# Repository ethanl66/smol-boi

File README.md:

# Smol boi

Custom 40% Keyboard PCB design files designed with KiCad 5.1.4. 

## Description

Smol Boi is a custom personal 40% keyboard PCB designed to provide a compact and efficient layout. This repository contains the KiCad design files including schematic and layout.
Firmware can be found at https://github.com/ethanl66/smolboi-firmware-v1.0

## Features

- 40% layout
- Custom layout with 46 keys
- USB-C connnectivity
- Flashable with DFU mode using USB-C
- Planned features for V2.0: LED indicators, hot-swap sockets, Bluetooth/2.4 GHz dongle, daughterboard, knob

## Contents

- `smolboi-pcb.sch`: Contains the PCB schematic
- `smolboi-pcb.kicad_pcb`: Contains the routing layout

## Acknowledgments

- Inspired by the community of keyboard enthusiasts
- Would not have been possible without r/MechanicalKeyboards

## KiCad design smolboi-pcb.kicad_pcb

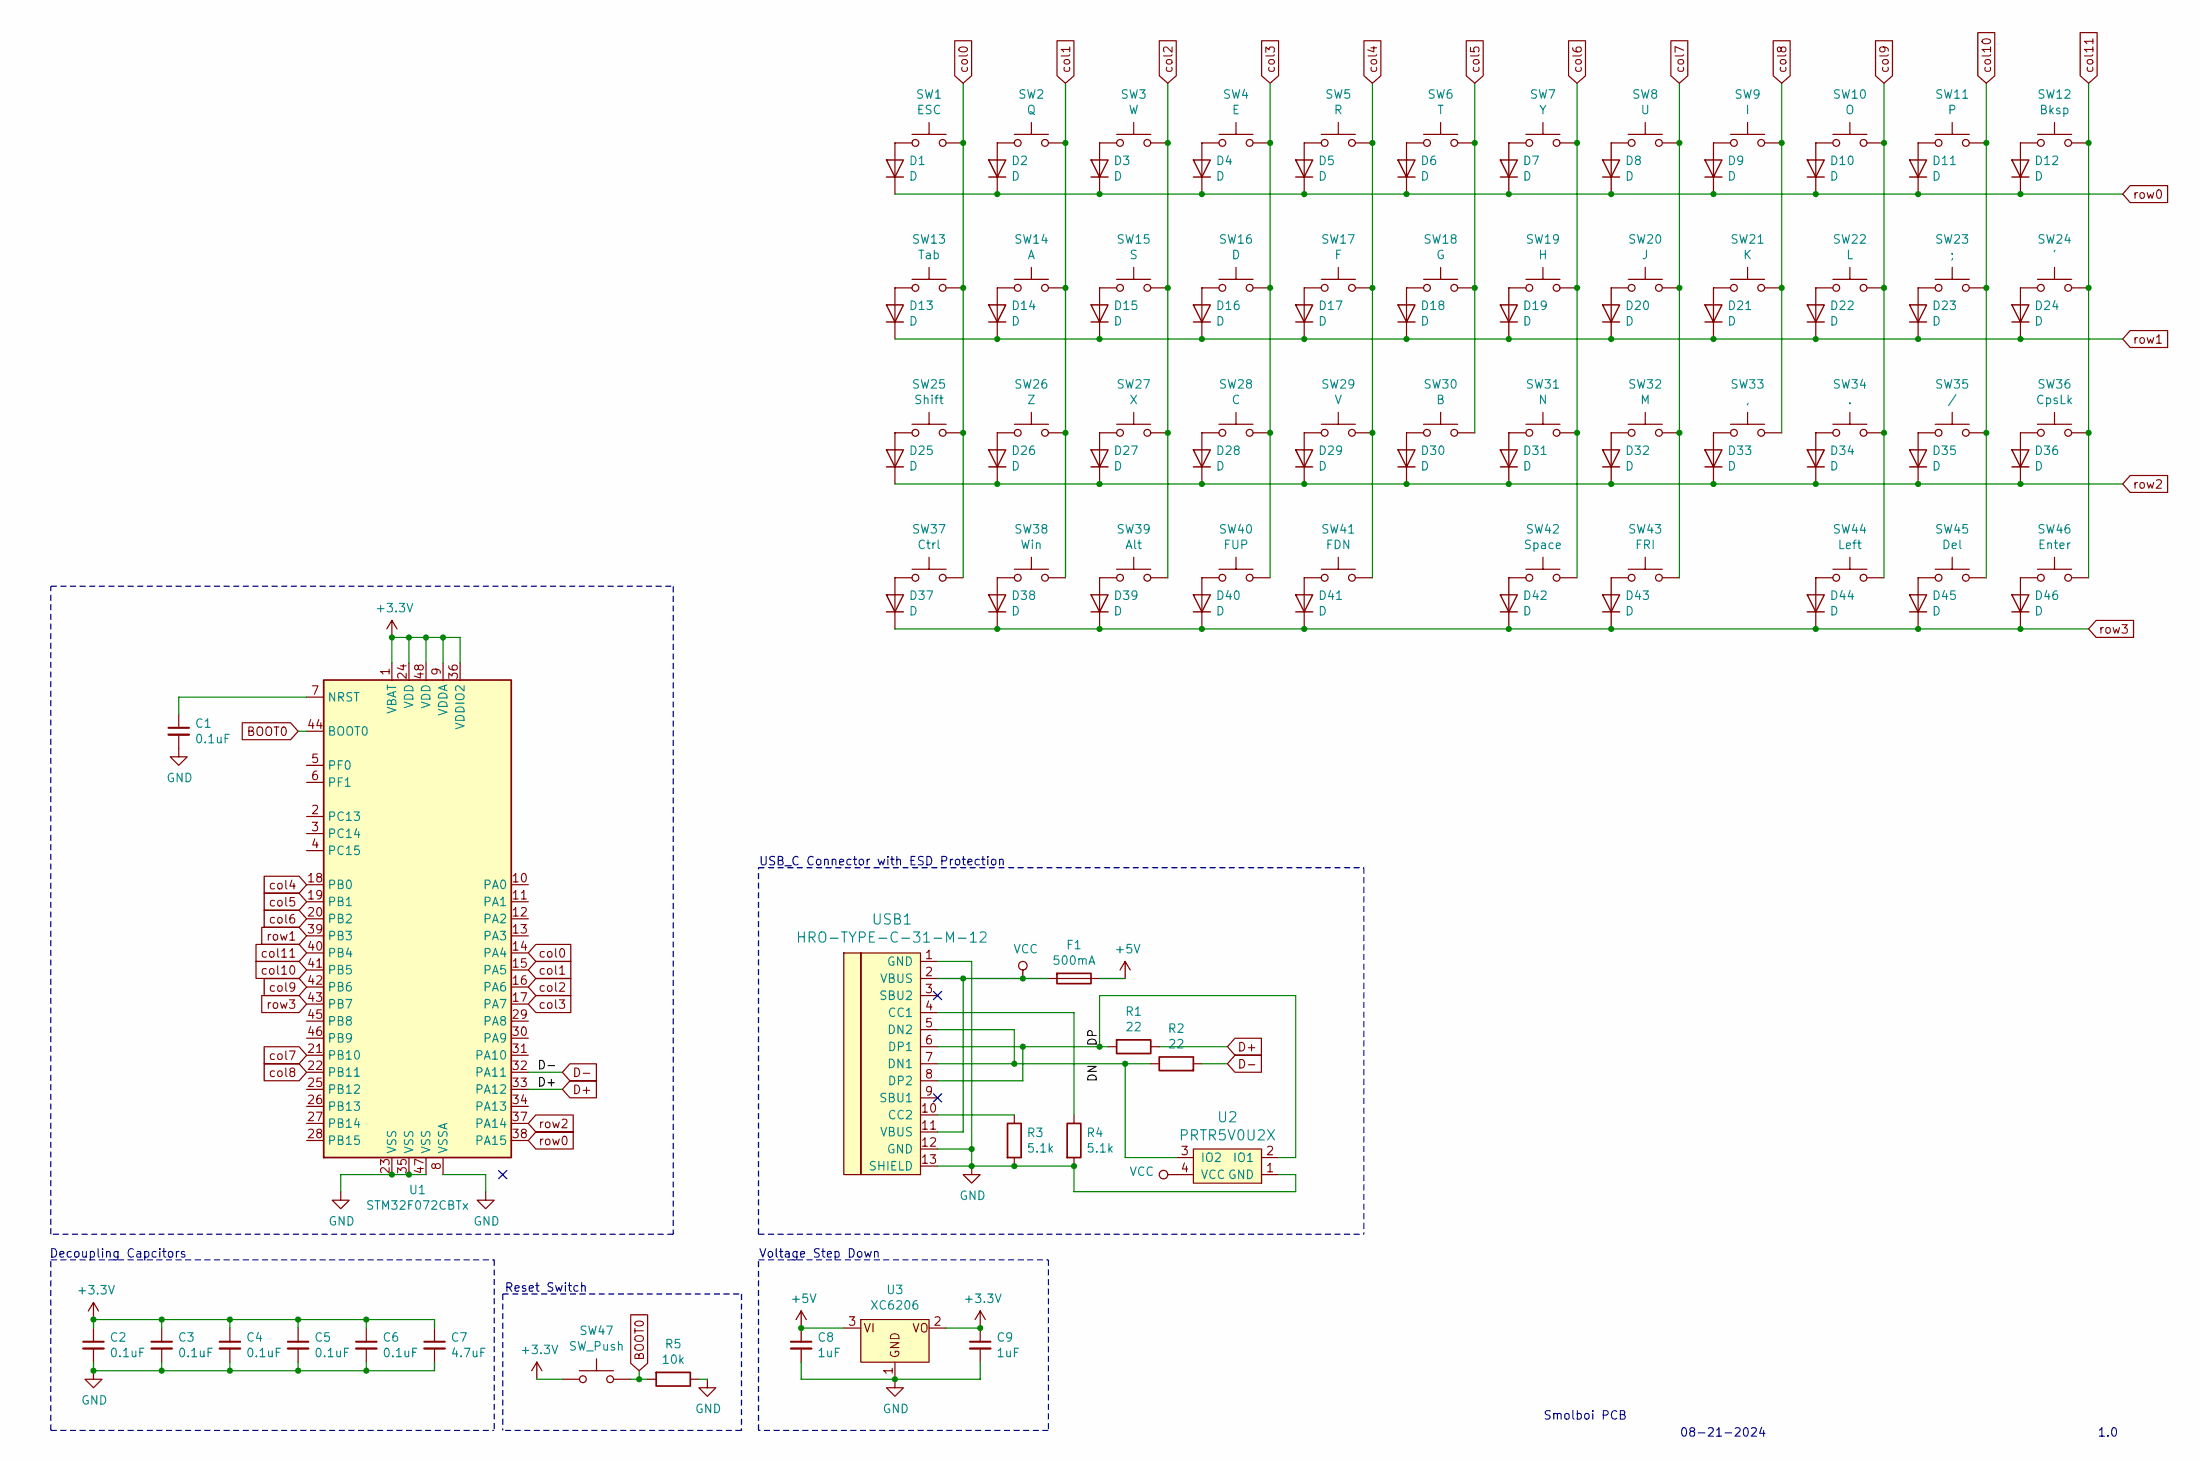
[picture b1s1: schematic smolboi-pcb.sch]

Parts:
C1, C2, C3, C4, C5, C6: 0.1uF; C_0402_1005Metric; LCSC C307331
C7: 4.7uF; C_0402_1005Metric; LCSC C23733
C8, C9: 1uF; C_0402_1005Metric; LCSC C52923
D1, D2, D3, D4, D5, D6, D7, D8, D9, D10, D11, D12, D13, D14, D15, D16, D17, D18, D19, D20, D21, D22, D23, D24, D25, D26, D27, D28, D29, D30, D31, D32, D33, D34, D35, D36, D37, D38, D39, D40, D41, D42, D43, D44, D45, D46: D; D_SOD-123; LCSC C77978
F1: 500mA; Fuse_1206_3216Metric; LCSC C70069
R1, R2: 22; R_0402_1005Metric; LCSC C6117666
R3, R4: 5.1k; R_0402_1005Metric; LCSC C400635
R5: 10k; R_0402_1005Metric; LCSC C850723
SW1: ESC; MXOnly-1U-NoLED
SW2: Q; MXOnly-1U-NoLED
SW3: W; MXOnly-1U-NoLED
SW4: E; MXOnly-1U-NoLED
SW5: R; MXOnly-1U-NoLED
SW6: T; MXOnly-1U-NoLED
SW7: Y; MXOnly-1U-NoLED
SW8: U; MXOnly-1U-NoLED
SW9: I; MXOnly-1U-NoLED
SW10: O; MXOnly-1U-NoLED
SW11: P; MXOnly-1U-NoLED
SW12: Bksp; MXOnly-1.75U-NoLED
SW13: Tab; MXOnly-1.25U-NoLED
SW14: A; MXOnly-1U-NoLED
SW15: S; MXOnly-1U-NoLED
SW16: D; MXOnly-1U-NoLED
SW17: F; MXOnly-1U-NoLED
SW18: G; MXOnly-1U-NoLED
SW19: H; MXOnly-1U-NoLED
SW20: J; MXOnly-1U-NoLED
SW21: K; MXOnly-1U-NoLED
SW22: L; MXOnly-1U-NoLED
SW23: ;; MXOnly-1U-NoLED
SW24: '; MXOnly-1.5U-NoLED
SW25: Shift; MXOnly-1.75U-NoLED
SW26: Z; MXOnly-1U-NoLED
SW27: X; MXOnly-1U-NoLED
SW28: C; MXOnly-1U-NoLED
SW29: V; MXOnly-1U-NoLED
SW30: B; MXOnly-1U-NoLED
SW31: N; MXOnly-1U-NoLED
SW32: M; MXOnly-1U-NoLED
SW33: ,; MXOnly-1U-NoLED
SW34: .; MXOnly-1U-NoLED
SW35: /; MXOnly-1U-NoLED
SW36: CpsLk; MXOnly-1U-NoLED
SW37: Ctrl; MXOnly-1.25U-NoLED
SW38: Win; MXOnly-1.25U-NoLED
SW39: Alt; MXOnly-1.25U-NoLED
SW40: FUP; MXOnly-1U-NoLED
SW41: FDN; MXOnly-1U-NoLED
SW42: Space; MXOnly-2U-NoLED
SW43: FRI; MXOnly-1U-NoLED
SW44: Left; MXOnly-1U-NoLED
SW45: Del; MXOnly-1U-NoLED
SW46: Enter; MXOnly-1U-NoLED
SW47: SW_Push; SW_SPST_SKQG_WithStem; LCSC C115351
U1: STM32F072CBTx; LQFP-48_7x7mm_P0.5mm; LCSC C81720
U2: PRTR5V0U2X; SOT143B; LCSC C12333
U3: XC6206; SOT-23; LCSC C5446
USB1: HRO-TYPE-C-31-M-12; HRO-TYPE-C-31-M-12-Assembly; LCSC C165948

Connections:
+3V3: C2.1, C3.1, C4.1, C5.1, C6.1, C7.1, C9.1, SW47.1, U1.1 (VBAT), U1.9 (VDDA), U1.24 (VDD), U1.36 (VDDIO2), U1.48 (VDD), U3.2
+5V: C8.1, F1.1, U3.3
/DN: R2.1, U2.3 (IO2), USB1.5 (DN2), USB1.7 (DN1)
/DP: R1.2, U2.2 (IO1), USB1.6 (DP1), USB1.8 (DP2)
BOOT0: R5.2, SW47.2, U1.44 (BOOT0)
D+: R1.1, U1.33 (PA12)
D-: R2.2, U1.32 (PA11)
GND: C1.2, C2.2, C3.2, C4.2, C5.2, C6.2, C7.2, C8.2, C9.2, R3.2, R4.2, R5.1, U1.8 (VSSA), U1.23 (VSS), U1.35 (VSS), U1.47 (VSS), U2.1 (GND), U3.1, USB1.1 (GND), USB1.12 (GND), USB1.13 (SHIELD)
unnamed: C1.1, U1.7 (NRST)
unnamed: D1.2 (A), SW1.1
unnamed: D2.2 (A), SW2.1
unnamed: D3.2 (A), SW3.1
unnamed: D4.2 (A), SW4.1
unnamed: D5.2 (A), SW5.1
unnamed: D6.2 (A), SW6.1
unnamed: D7.2 (A), SW7.1
unnamed: D8.2 (A), SW8.1
unnamed: D9.2 (A), SW9.1
unnamed: D10.2 (A), SW10.1
unnamed: D11.2 (A), SW11.1
unnamed: D12.2 (A), SW12.1
unnamed: D13.2 (A), SW13.1
unnamed: D14.2 (A), SW14.1
unnamed: D15.2 (A), SW15.1
unnamed: D16.2 (A), SW16.1
unnamed: D17.2 (A), SW17.1
unnamed: D18.2 (A), SW18.1
unnamed: D19.2 (A), SW19.1
unnamed: D20.2 (A), SW20.1
unnamed: D21.2 (A), SW21.1
unnamed: D22.2 (A), SW22.1
unnamed: D23.2 (A), SW23.1
unnamed: D24.2 (A), SW24.1
unnamed: D25.2 (A), SW25.1
unnamed: D26.2 (A), SW26.1
unnamed: D27.2 (A), SW27.1
unnamed: D28.2 (A), SW28.1
unnamed: D29.2 (A), SW29.1
unnamed: D30.2 (A), SW30.1
unnamed: D31.2 (A), SW31.1
unnamed: D32.2 (A), SW32.1
unnamed: D33.2 (A), SW33.1
unnamed: D34.2 (A), SW34.1
unnamed: D35.2 (A), SW35.1
unnamed: D36.2 (A), SW36.1
unnamed: D37.2 (A), SW37.1
unnamed: D38.2 (A), SW38.1
unnamed: D39.2 (A), SW39.1
unnamed: D40.2 (A), SW40.1
unnamed: D41.2 (A), SW41.1
unnamed: D42.2 (A), SW42.1
unnamed: D43.2 (A), SW43.1
unnamed: D44.2 (A), SW44.1
unnamed: D45.2 (A), SW45.1
unnamed: D46.2 (A), SW46.1
unnamed: R3.1, USB1.10 (CC2)
unnamed: R4.1, USB1.4 (CC1)
VCC: F1.2, U2.4 (VCC), USB1.2 (VBUS), USB1.11 (VBUS)
col0: SW1.2, SW13.2, SW25.2, SW37.2, U1.14 (PA4)
col1: SW2.2, SW14.2, SW26.2, SW38.2, U1.15 (PA5)
col2: SW3.2, SW15.2, SW27.2, SW39.2, U1.16 (PA6)
col3: SW4.2, SW16.2, SW28.2, SW40.2, U1.17 (PA7)
col4: SW5.2, SW17.2, SW29.2, SW41.2, U1.18 (PB0)
col5: SW6.2, SW18.2, SW30.2, U1.19 (PB1)
col6: SW7.2, SW19.2, SW31.2, SW42.2, U1.20 (PB2)
col7: SW8.2, SW20.2, SW32.2, SW43.2, U1.21 (PB10)
col8: SW9.2, SW21.2, SW33.2, U1.22 (PB11)
col9: SW10.2, SW22.2, SW34.2, SW44.2, U1.42 (PB6)
col10: SW11.2, SW23.2, SW35.2, SW45.2, U1.41 (PB5)
col11: SW12.2, SW24.2, SW36.2, SW46.2, U1.40 (PB4)
row0: D1.1 (K), D2.1 (K), D3.1 (K), D4.1 (K), D5.1 (K), D6.1 (K), D7.1 (K), D8.1 (K), D9.1 (K), D10.1 (K), D11.1 (K), D12.1 (K), U1.38 (PA15)
row1: D13.1 (K), D14.1 (K), D15.1 (K), D16.1 (K), D17.1 (K), D18.1 (K), D19.1 (K), D20.1 (K), D21.1 (K), D22.1 (K), D23.1 (K), D24.1 (K), U1.39 (PB3)
row2: D25.1 (K), D26.1 (K), D27.1 (K), D28.1 (K), D29.1 (K), D30.1 (K), D31.1 (K), D32.1 (K), D33.1 (K), D34.1 (K), D35.1 (K), D36.1 (K), U1.37 (PA14)
row3: D37.1 (K), D38.1 (K), D39.1 (K), D40.1 (K), D41.1 (K), D42.1 (K), D43.1 (K), D44.1 (K), D45.1 (K), D46.1 (K), U1.43 (PB7)

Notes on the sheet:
Smolboi PCB
08-21-2024
1.0
USB_C Connector with ESD Protection
Voltage Step Down
Decoupling Capcitors
Reset Switch

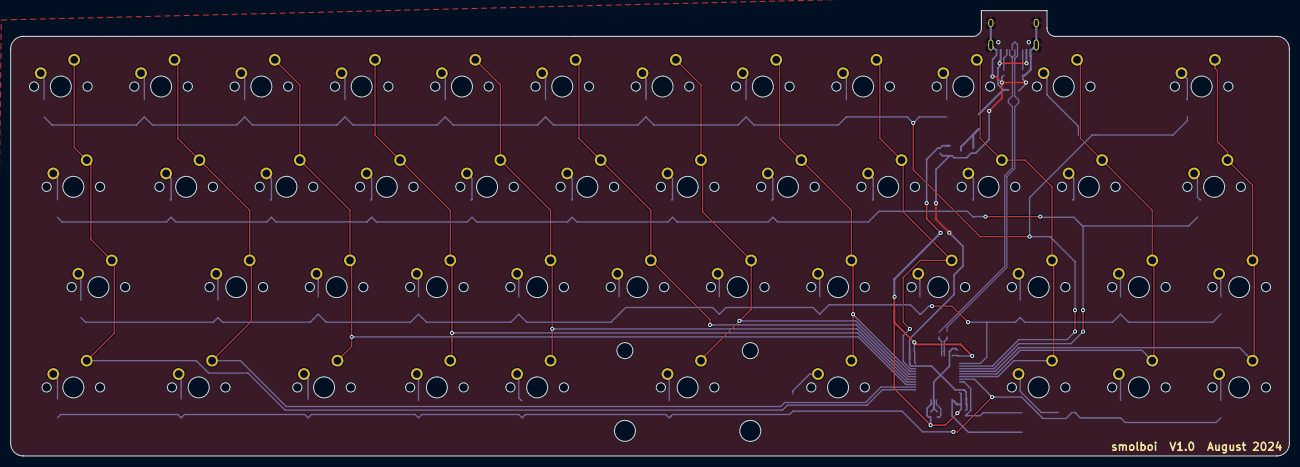
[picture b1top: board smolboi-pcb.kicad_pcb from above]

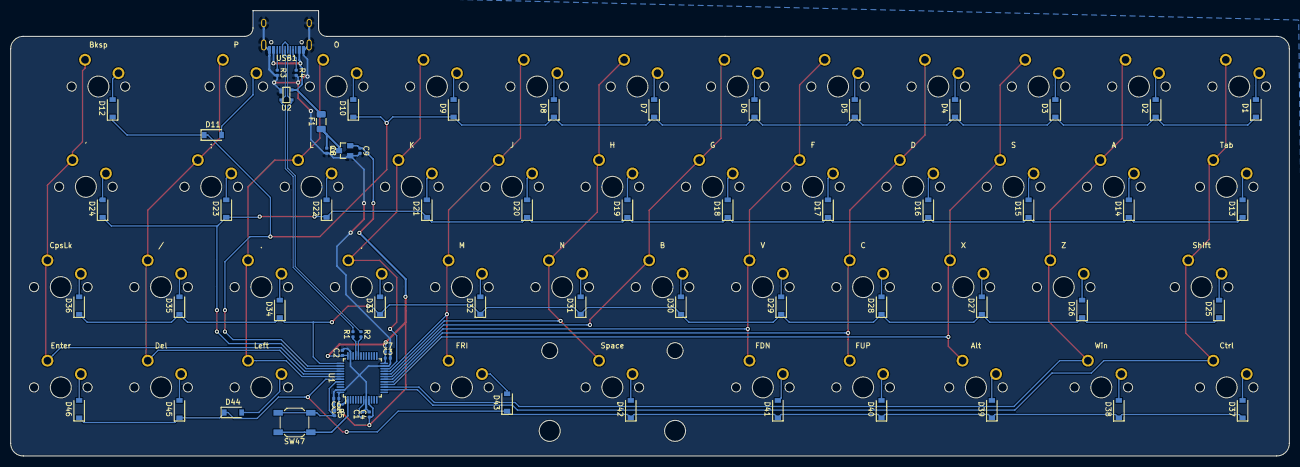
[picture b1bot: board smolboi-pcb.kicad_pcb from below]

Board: 2 copper layers, 242.9 x 84.6 mm, 112 parts (66 on the bottom side), 74 nets.

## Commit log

2024-07-20 add 3 submodules
2024-07-21 add 3 libraries to kicad
2024-07-21 schematic work, add scottokeebs submodule
2024-07-21 schematic before check
2024-07-23 ceramic oscillator, major schematic modules finalized
2024-08-22 up to finish diff pair routing
2024-08-24 staggered layout, routed diff pair on right side
2024-08-25 gnd fill around oscillator, all pwr routed, NRST vias
2024-08-25 routed matrix
2024-08-25 inc USB C solder pad margin
2024-08-25 replaced with STM32F072CBT6, rerouted
2024-08-25 ground fills
2024-08-25 DRC, final aesthetic touches
2024-08-25 gerbers and drill in zip
2024-08-25 jlcpcb bom and pos files
2024-08-25 final
2025-02-14 update for readme
